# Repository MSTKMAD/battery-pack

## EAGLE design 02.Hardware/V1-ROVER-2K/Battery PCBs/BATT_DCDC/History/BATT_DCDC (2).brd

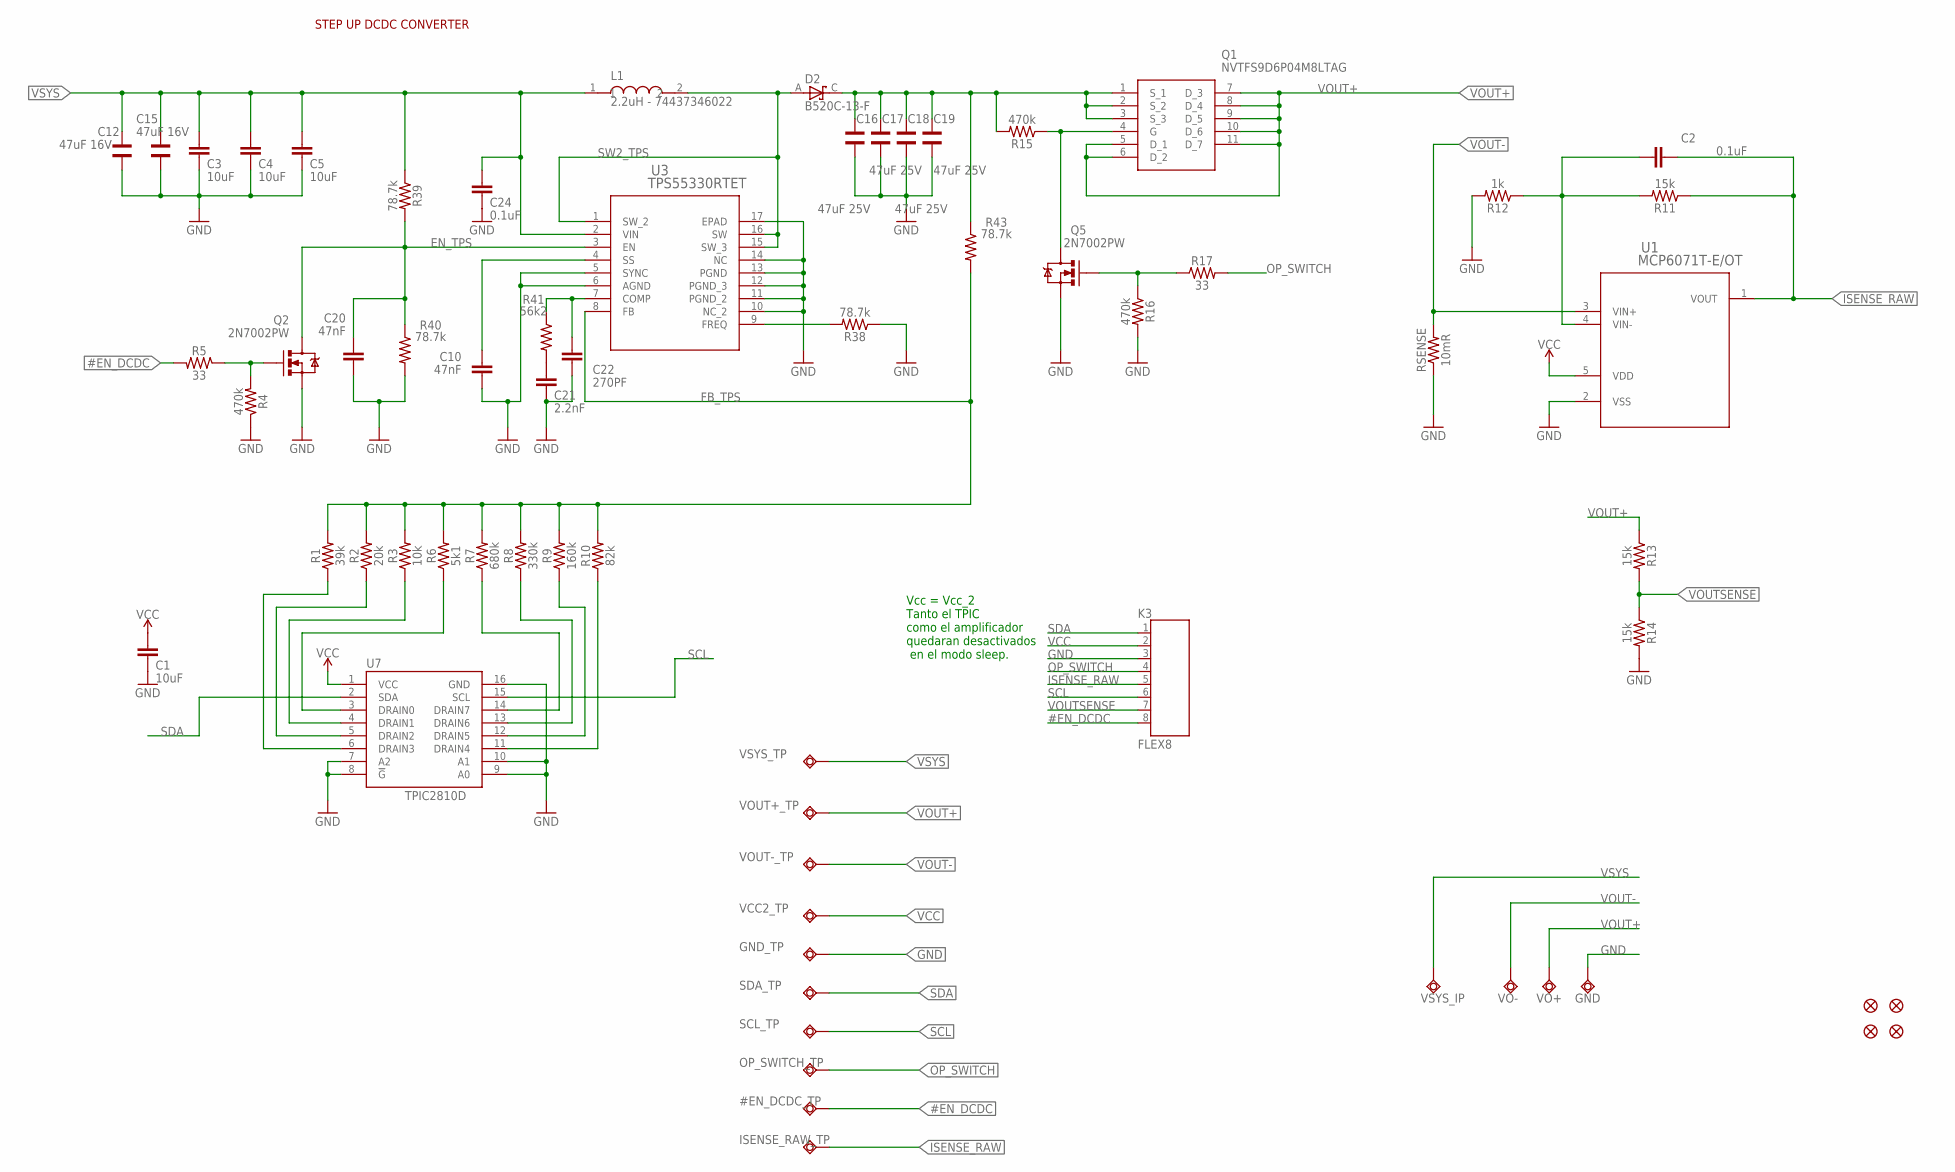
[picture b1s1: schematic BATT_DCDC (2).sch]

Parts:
#EN_DCDC_TP: TESTPAD_TPSQB1,27; TESTPAD_B1,27
C1, C3, C4, C5: 10uF; 0805
C2, C24: 0.1uF; 0603
C10, C20: 47nF; 0603
C12, C15: 47uF 16V; WCAP-CSGP_1210
C16, C17, C18, C19: 47uF 25V; WCAP-CSGP_1210
C21: 2.2nF; 0603
C22: 270PF; 0603
D2: B520C-13-F; DIOM7959X250N
GND: TESTPAD_TPSQTP15SQ; TESTPAD_TP15SQ
GND_TP: TESTPAD_TPSQB1,27; TESTPAD_B1,27
ISENSE_RAW_TP: TESTPAD_TPSQB1,27; TESTPAD_B1,27
K3: FLEX8
L1: 2.2uH - 74437346022; INDM7366X500
OP_SWITCH_TP: TESTPAD_TPSQB1,27; TESTPAD_B1,27
Q1: NVTFS9D6P04M8LTAG; NVTFS5124PLTWG
Q2, Q5: 2N7002PW; SOT323
R1: 39k; 0402
R2: 20k; 0402
R3: 10k; 0402
R4, R15, R16: 470k; 0402
R5, R17: 33; 0402
R6: 5k1; 0402
R7: 680k; 0402
R8: 330k; 0402
R9: 160k; 0402
R10: 82k; 0402
R11, R13, R14: 15k; 0402
R12: 1k; 0402
R38, R39, R40, R43: 78.7k; 0402
R41: 56k2; 0402
RSENSE: 10mR; 0603
SCL_TP: TESTPAD_TPSQB1,27; TESTPAD_B1,27
SDA_TP: TESTPAD_TPSQB1,27; TESTPAD_B1,27
U1: MCP6071T-E/OT; SOT-23-5_MC_MCH
U3: TPS55330RTET; RTE16_1P66X1P66_TEX
U7: TPIC2810D; SO16
U$1, U$2, U$34, U$35: FIDUCIAL""; FIDUCIAL_1MM
VCC2_TP: TESTPAD_TPSQB1,27; TESTPAD_B1,27
VO+: TESTPAD_TPSQTP15SQ; TESTPAD_TP15SQ
VO-: TESTPAD_TPSQTP15SQ; TESTPAD_TP15SQ
VOUT+_TP: TESTPAD_TPSQB1,27; TESTPAD_B1,27
VOUT-_TP: TESTPAD_TPSQB1,27; TESTPAD_B1,27
VSYS_IP: TESTPAD_TPSQTP15SQ; TESTPAD_TP15SQ
VSYS_TP: TESTPAD_TPSQB1,27; TESTPAD_B1,27

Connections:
#EN_DCDC: #EN_DCDC_TP.TP, K3.8, R5.2
COMP_TPS: C22.2, R41.1, U3.7 (COMP)
EN_TPS: C20.1, Q2.3 (D), R39.2, R40.1, U3.3 (EN)
FB_TPS: R1.2, R2.2, R3.2, R6.2, R7.2, R8.2, R9.2, R10.2, R43.2, U3.8 (FB)
FREQ_TPS: R38.2, U3.9 (FREQ)
GND: C1.1, C3.1, C4.1, C5.1, C10.2, C12.1, C15.1, C16.1, C17.1, C18.1, C19.1, C20.2, C21.1, C22.1, C24.1, GND.TP, GND_TP.TP, K3.3, Q2.2 (S), Q5.2 (S), R4.1, R12.2, R14.2, R16.2, R38.1, R40.2, RSENSE.1, U1.2 (VSS), U3.5 (SYNC), U3.6 (AGND), U3.10 (NC_2), U3.11 (PGND_2), U3.12 (PGND_3), U3.13 (PGND), U3.14 (NC), U3.17 (EPAD), U7.7 (A2), U7.8 (!G), U7.9 (A0), U7.10 (A1), U7.16 (GND)
ISENSE_RAW: C2.1, ISENSE_RAW_TP.TP, K3.5, R11.1, U1.1 (VOUT)
unnamed: C2.2, R11.2, R12.1, U1.4 (VIN-)
unnamed: R1.1, U7.6 (DRAIN3)
unnamed: R2.1, U7.5 (DRAIN2)
unnamed: Q2.1 (G), R4.2, R5.1
unnamed: R3.1, U7.4 (DRAIN1)
unnamed: R6.1, U7.3 (DRAIN0)
unnamed: R7.1, U7.14 (DRAIN7)
unnamed: Q1.4 (G), Q5.3 (D), R15.1
unnamed: R8.1, U7.13 (DRAIN6)
unnamed: R9.1, U7.12 (DRAIN5)
unnamed: R10.1, U7.11 (DRAIN4)
unnamed: Q5.1 (G), R16.1, R17.1
unnamed: C10.1, U3.4 (SS)
unnamed: C21.2, R41.2
OP_SWITCH: K3.4, OP_SWITCH_TP.TP, R17.2
SCL: K3.6, SCL_TP.TP, U7.15 (SCL)
SDA: K3.1, SDA_TP.TP, U7.2 (SDA)
SW2_TPS: D2.A, L1.2, U3.1 (SW_2), U3.15 (SW_3), U3.16 (SW)
VCC: C1.2, K3.2, U1.5 (VDD), U7.1 (VCC), VCC2_TP.TP
VOUT+: Q1.5 (D_1), Q1.6 (D_2), Q1.7 (D_3), Q1.8 (D_4), Q1.9 (D_5), Q1.10 (D_6), Q1.11 (D_7), R13.1, VO+.TP, VOUT+_TP.TP
VOUT-: RSENSE.2, U1.3 (VIN+), VO-.TP, VOUT-_TP.TP
VOUTSENSE: K3.7, R13.2, R14.1
VSOURCE: C16.2, C17.2, C18.2, C19.2, D2.C, Q1.1 (S_1), Q1.2 (S_2), Q1.3 (S_3), R15.2, R43.1
VSYS: C3.2, C4.2, C5.2, C12.2, C15.2, C24.2, L1.1, R39.1, U3.2 (VIN), VSYS_IP.TP, VSYS_TP.TP

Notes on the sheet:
STEP UP DCDC CONVERTER
Vcc = Vcc_2 Tanto el TPIC como el amplificador quedaran desactivados en el modo sleep.

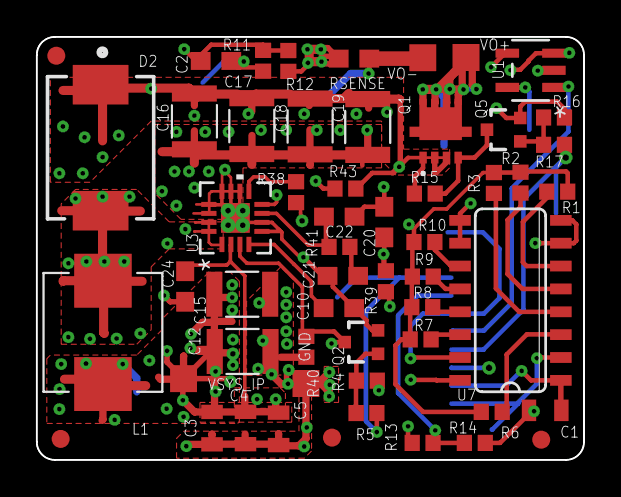
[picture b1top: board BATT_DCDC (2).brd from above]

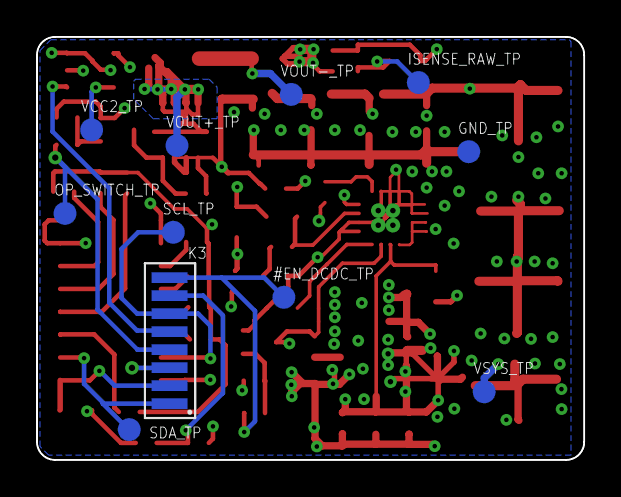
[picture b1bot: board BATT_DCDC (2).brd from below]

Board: 4 copper layers, 30.4 x 23.5 mm, 66 parts (11 on the bottom side), 31 nets.

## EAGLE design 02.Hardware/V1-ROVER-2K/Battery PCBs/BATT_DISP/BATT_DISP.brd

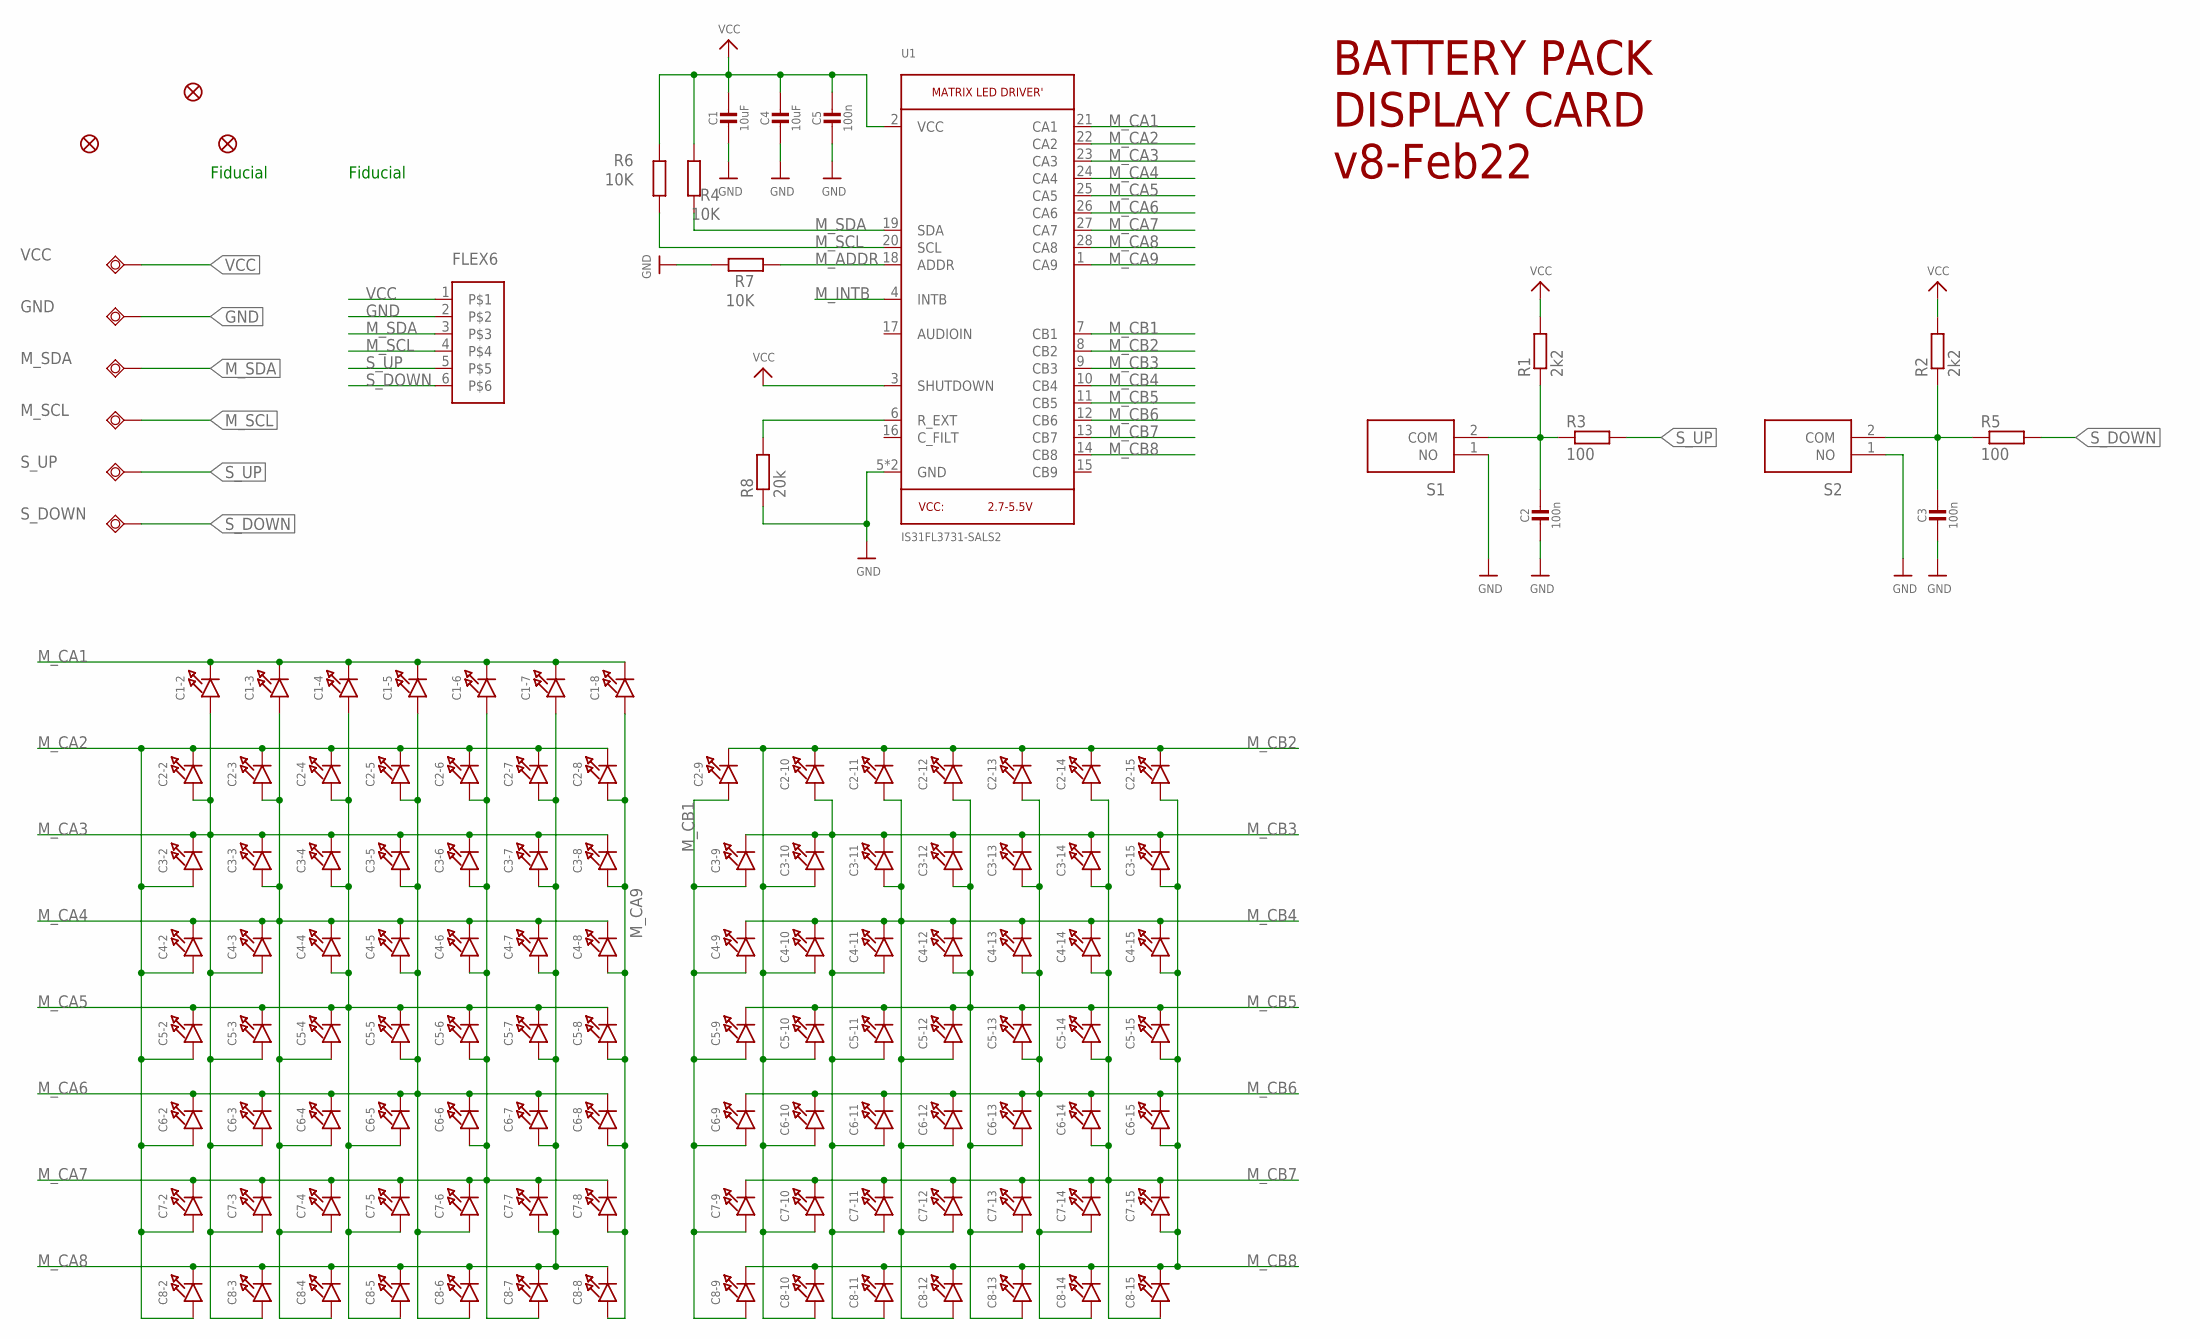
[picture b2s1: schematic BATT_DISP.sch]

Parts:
C1, C4: 10uF; 0805-NO
C1-2, C1-3, C1-4, C1-5, C1-6, C1-7, C1-8, C2-2, C2-3, C2-4, C2-5, C2-6, C2-7, C2-8, C2-9, C2-10, C2-11, C2-12, C2-13, C2-14, C2-15, C3-2, C3-3, C3-4, C3-5, C3-6, C3-7, C3-8, C3-9, C3-10, C3-11, C3-12, C3-13, C3-14, C3-15, C4-2, C4-3, C4-4, C4-5, C4-6, C4-7, C4-8, C4-9, C4-10, C4-11, C4-12, C4-13, C4-14, C4-15, C5-2, C5-3, C5-4, C5-5, C5-6, C5-7, C5-8, C5-9, C5-10, C5-11, C5-12, C5-13, C5-14, C5-15, C6-2, C6-3, C6-4, C6-5, C6-6, C6-7, C6-8, C6-9, C6-10, C6-11, C6-12, C6-13, C6-14, C6-15, C7-2, C7-3, C7-4, C7-5, C7-6, C7-7, C7-8, C7-9, C7-10, C7-11, C7-12, C7-13, C7-14, C7-15, C8-2, C8-3, C8-4, C8-5, C8-6, C8-7, C8-8, C8-9, C8-10, C8-11, C8-12, C8-13, C8-14, C8-15: LED0402_NOOUTLINE; CHIPLED_0402_NOOUTLINE
C2, C3, C5: 100n; 0805-NO
FD1: FIDUCIALUFIDUCIAL; FIDUCIAL-MICRO
FD2, FD3: FIDUCIAL""; FIDUCIAL_1MM
GND: TESTPAD_TPSQB1,27; TESTPAD_B1,27
K1: FLEX6
M_SCL: TESTPAD_TPSQB1,27; TESTPAD_B1,27
M_SDA: TESTPAD_TPSQB1,27; TESTPAD_B1,27
R1, R2: 2k2; R0603
R3, R5: 100; R0603
R4, R6, R7: 10K; R0603
R8: 20k; R0603
S1, S2: KXT311LHS
S_DOWN: TESTPAD_TPSQB1,27; TESTPAD_B1,27
S_UP: TESTPAD_TPSQB1,27; TESTPAD_B1,27
U1: IS31FL3731-SALS2; QFN28_4MM_0.4MM
VCC: TESTPAD_TPSQB1,27; TESTPAD_B1,27

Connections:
GND: C1.2, C2.2, C3.2, C4.2, C5.2, GND.TP, K1.2, R7.2, R8.1, S1.1 (NO), S2.1 (NO), U1.5 (GND), U1.THERMAL (GND)
M_ADDR: R7.1, U1.18 (ADDR)
M_CA1: C1-2.C, C1-3.C, C1-4.C, C1-5.C, C1-6.C, C1-7.C, C1-8.C, U1.21 (CA1)
M_CA2: C2-2.C, C2-3.C, C2-4.C, C2-5.C, C2-6.C, C2-7.C, C2-8.C, C3-2.A, C4-2.A, C5-2.A, C6-2.A, C7-2.A, C8-2.A, U1.22 (CA2)
M_CA3: C1-2.A, C2-2.A, C3-2.C, C3-3.C, C3-4.C, C3-5.C, C3-6.C, C3-7.C, C3-8.C, C4-3.A, C5-3.A, C6-3.A, C7-3.A, C8-3.A, U1.23 (CA3)
M_CA4: C1-3.A, C2-3.A, C3-3.A, C4-2.C, C4-3.C, C4-4.C, C4-5.C, C4-6.C, C4-7.C, C4-8.C, C5-4.A, C6-4.A, C7-4.A, C8-4.A, U1.24 (CA4)
M_CA5: C1-4.A, C2-4.A, C3-4.A, C4-4.A, C5-2.C, C5-3.C, C5-4.C, C5-5.C, C5-6.C, C5-7.C, C5-8.C, C6-5.A, C7-5.A, C8-5.A, U1.25 (CA5)
M_CA6: C1-5.A, C2-5.A, C3-5.A, C4-5.A, C5-5.A, C6-2.C, C6-3.C, C6-4.C, C6-5.C, C6-6.C, C6-7.C, C6-8.C, C7-6.A, C8-6.A, U1.26 (CA6)
M_CA7: C1-6.A, C2-6.A, C3-6.A, C4-6.A, C5-6.A, C6-6.A, C7-2.C, C7-3.C, C7-4.C, C7-5.C, C7-6.C, C7-7.C, C7-8.C, C8-7.A, U1.27 (CA7)
M_CA8: C1-7.A, C2-7.A, C3-7.A, C4-7.A, C5-7.A, C6-7.A, C7-7.A, C8-2.C, C8-3.C, C8-4.C, C8-5.C, C8-6.C, C8-7.C, C8-8.C, U1.28 (CA8)
M_CA9: C1-8.A, C2-8.A, C3-8.A, C4-8.A, C5-8.A, C6-8.A, C7-8.A, C8-8.A, U1.1 (CA9)
M_CB1: C2-9.A, C3-9.A, C4-9.A, C5-9.A, C6-9.A, C7-9.A, C8-9.A, U1.7 (CB1)
M_CB2: C2-9.C, C2-10.C, C2-11.C, C2-12.C, C2-13.C, C2-14.C, C2-15.C, C3-10.A, C4-10.A, C5-10.A, C6-10.A, C7-10.A, C8-10.A, U1.8 (CB2)
M_CB3: C2-10.A, C3-9.C, C3-10.C, C3-11.C, C3-12.C, C3-13.C, C3-14.C, C3-15.C, C4-11.A, C5-11.A, C6-11.A, C7-11.A, C8-11.A, U1.9 (CB3)
M_CB4: C2-11.A, C3-11.A, C4-9.C, C4-10.C, C4-11.C, C4-12.C, C4-13.C, C4-14.C, C4-15.C, C5-12.A, C6-12.A, C7-12.A, C8-12.A, U1.10 (CB4)
M_CB5: C2-12.A, C3-12.A, C4-12.A, C5-9.C, C5-10.C, C5-11.C, C5-12.C, C5-13.C, C5-14.C, C5-15.C, C6-13.A, C7-13.A, C8-13.A, U1.11 (CB5)
M_CB6: C2-13.A, C3-13.A, C4-13.A, C5-13.A, C6-9.C, C6-10.C, C6-11.C, C6-12.C, C6-13.C, C6-14.C, C6-15.C, C7-14.A, C8-14.A, U1.12 (CB6)
M_CB7: C2-14.A, C3-14.A, C4-14.A, C5-14.A, C6-14.A, C7-9.C, C7-10.C, C7-11.C, C7-12.C, C7-13.C, C7-14.C, C7-15.C, C8-15.A, U1.13 (CB7)
M_CB8: C2-15.A, C3-15.A, C4-15.A, C5-15.A, C6-15.A, C7-15.A, C8-9.C, C8-10.C, C8-11.C, C8-12.C, C8-13.C, C8-14.C, C8-15.C, U1.14 (CB8)
M_INTB: U1.4 (INTB)
M_SCL: K1.4, M_SCL.TP, R6.1, U1.20 (SCL)
M_SDA: K1.3, M_SDA.TP, R4.1, U1.19 (SDA)
unnamed: C3.1, R2.1, R5.1, S2.2 (COM)
unnamed: C2.1, R1.1, R3.1, S1.2 (COM)
R_EXT: R8.2, U1.6 (R_EXT)
S_DOWN: K1.6, R5.2, S_DOWN.TP
S_UP: K1.5, R3.2, S_UP.TP
VCC: C1.1, C4.1, C5.1, K1.1, R1.2, R2.2, R4.2, R6.2, U1.2 (VCC), U1.3 (SHUTDOWN), VCC.TP

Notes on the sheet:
Fiducial
BATTERY PACK DISPLAY CARD v8-Feb22

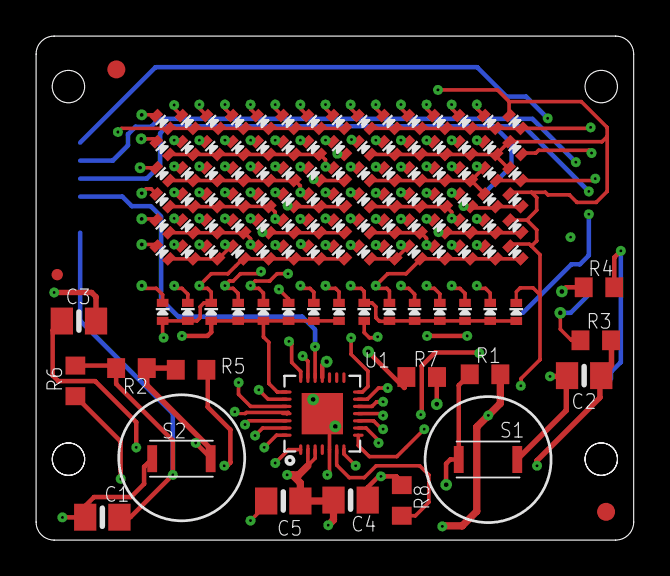
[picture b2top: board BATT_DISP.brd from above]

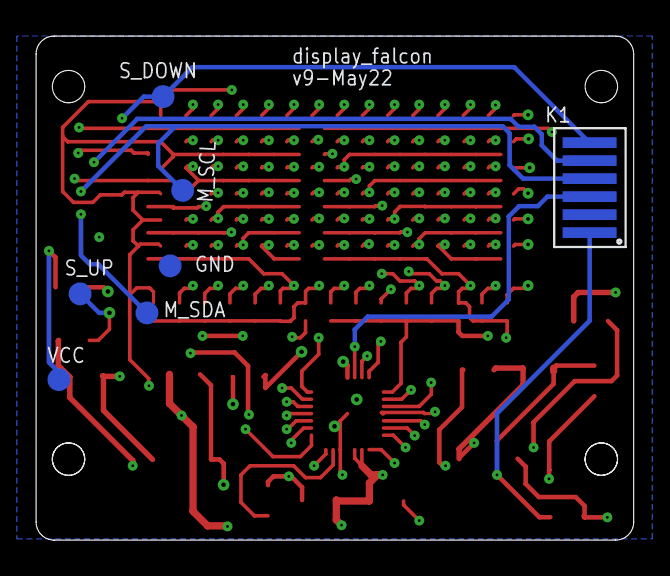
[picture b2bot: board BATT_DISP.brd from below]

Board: 4 copper layers, 33.2 x 28.0 mm, 131 parts (7 on the bottom side), 27 nets.

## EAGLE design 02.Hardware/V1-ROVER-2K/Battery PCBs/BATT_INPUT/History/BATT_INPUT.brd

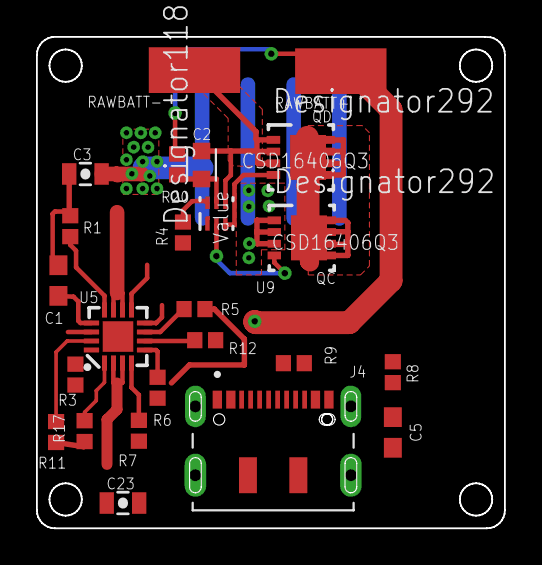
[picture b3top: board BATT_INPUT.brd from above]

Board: 4 copper layers, 26.0 x 27.3 mm, 25 parts (1 on the bottom side), 25 nets.

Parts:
C1: 1.0uF; 0603
C2: 100nF; CAPC1608X85
C3, C23: 10uF / 10V; 0805-CAP
C5: 0.1uF; 0603
J1: 70AAJ-4-M0; 70AAJ4M0
J4: DX07S016JA1R1500; JAE_DX07S016JA1R1500
QC: CSD16406Q3; DQG0008A
QD: CSD16406Q3; DQG0008A
R1: 1K1; 0402
R3: 590; 0402
R4: 2K2; 0402
R5: 1K; 0402
R6, R7, R11, R12, R17: 10K; 0402
R8, R9: 5K1; 0402
R20: 330; 0402
RAWBATT+: SMD2,54-5,08
RAWBATT-: SMD2,54-5,08
U5: BQ24075; PVQFN-N16
U9: Value; DSE0006A

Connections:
!CE!: R7.2, U5.4
-: QC.5, QC.6, QC.7, QC.8, QC.9, QD.5, QD.6, QD.7, QD.8, QD.9
BATT+: C23.1, R20.2, RAWBATT+.1, U5.2, U5.3
BATT-: C2.2, QD.1, QD.2, QD.3, RAWBATT-.1, U9.4
D+: J4.5, J4.8
D-: J4.6, J4.7
EN1: R12.2, U5.6
EN2: R6.2, U5.5
GND: C1.2, C3.2, C5.2, C23.2, J1.3, J1.6, J4.1, J4.12, QC.1, QC.2, QC.3, R1.1, R3.1, R4.1, R7.1, R8.1, R9.1, R11.1, R12.1, R17.1, U5.8, U5.14, U5.EP
ILIM: R1.2, U5.12
ISET: R3.2, U5.16
unnamed: R5.1, U5.7
unnamed: J1.1, J1.8
unnamed: J1.2, J1.7
unnamed: J4.3, R9.2
unnamed: J4.9, R8.2
unnamed: C2.1, R20.1, U9.5
unnamed: R4.2, U9.6
unnamed: QC.4, U9.2
unnamed: QD.4, U9.3
SHLD: J4.S1, J4.S2, J4.S3, J4.S4, J4.S5, J4.S6
SYSOFF: R11.2, U5.15
TS1: R17.2, U5.1
VSYS: C3.1, J1.4, J1.5, R5.2, R6.1, U5.10, U5.11
V_USB: C1.1, C5.1, J4.2, J4.11, U5.13

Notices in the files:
parts and their libraries:
microbuilder: This work is placed in the public domain, and may be freely used for commercial and non-commercial work with the following conditions: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
SparkFun-Resistors: Licensing: Creative Commons ShareAlike 4.0 International - https://creativecommons.org/licenses/by-sa/4.0
